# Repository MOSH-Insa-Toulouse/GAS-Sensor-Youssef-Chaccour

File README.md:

# MICRO-CONTROLLERS AND OPEN-SOURCE HARDWARE - Gas Sensor and LoRa Communication - Arduino Shield
This project was realized as part of "Microcontrollers and Open-Source Hardware" by Youssef Chaccour

# Goal
The goal of this project is to design a complete printed circuit board (PCB).
The circuit is then used with an Arduino board and a LoRa.
The collected data will be sent via the LoRa protocol on the TTN platform (The Things Network).

# Equipment
- Shield Gas Sensor
- Arduino uno
- LoRa module RN2483 breakout

# Features
- Gas sensor with connection (Requiring completion AIME)
- Adaptation circuit of the gas sensor to the ADC of the Arduino UNO:
- Filtering noises containing 2 passive filters and an active filter with AOP LTC1050
- Anti-aliasing filtering to perform ADC sampling
- Adaptation of the caliber
 
# Contents
This project contains source code and design files:
- The schematic part, describing the implemented electronic circuit (components, routing of pins)
- The layout part, describing the shape of the map, the location of the various elements on it and the trajectory of the routing tracks.
- Arduino code for LoRa

# Schemas PCB
Schematic design:
Here are some features of the schema:
- The input resistor (R1) is a protection resistor, it protects the operational amplifier from electrostatic discharges. Moreover, it is associated with the capacitor C1 to filter the voltage noise.
- The circuit between the capacitor C1 and the resistor R2 allows us to filter the current noise.
- Resistor R3 is used to adapt our assembly to the correct size. The resistance R3 can be modified to better calibrate the assembly.
- I had set up an active filter thanks to the circuit between the capacitor C2 and the resistor R4 at the output of the amplifier.
The resistor R5 and the capacitor C4 constitute a low-pass filter at the output of the assembly.
Finally, the capacitor C3 filters the noise coming from the voltage input 5V.

# PCB footprint on KiCad
Layout Design:
In order to realize the footprint correctly, I had to put into practice the following points:
- I chose a track width of 0.8 mm, so that the builder can achieve it with his equipment.
- I decided to insert only the RN2483 Breakout plate connector to optimize footprint space. Especially since we consider that the RN2483 card will not be directly integrated on the shield but connected by wires (connector).
- I used a layer of GND on the back of the plate allowing us to further optimize our space by reducing the number of connections.

Also, I have attached solution of the “exercise 5” (In Real Folder and requested by Mr. Jeremie Grisolia), as this exercise summarize the hole course, choosing the best technology with the least error.

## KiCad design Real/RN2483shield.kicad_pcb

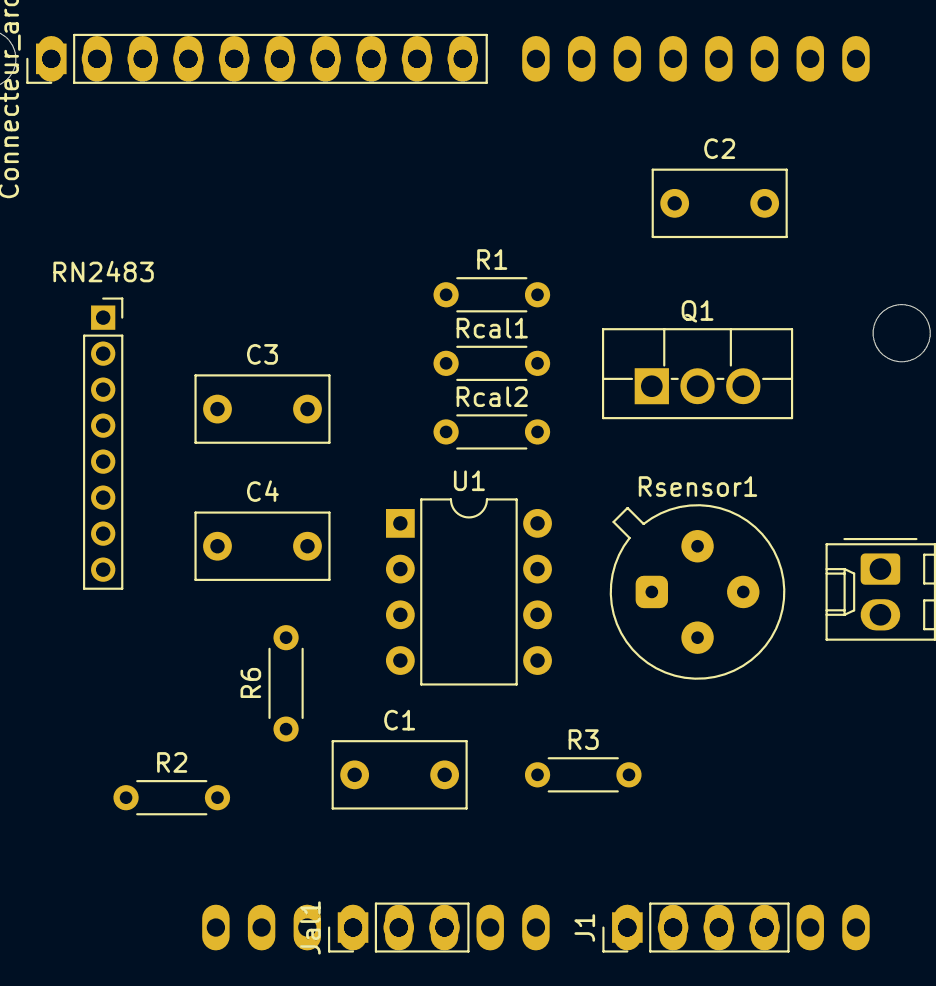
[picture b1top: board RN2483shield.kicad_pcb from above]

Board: 2 copper layers, 19 parts (0 on the bottom side), 14 nets, no tracks yet.

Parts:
C1, C2, C3: 100n; C_Rect_L7.2mm_W3.5mm_P5.00mm_FKS2_FKP2_MKS2_MKP2
C4: 1u; C_Rect_L7.2mm_W3.5mm_P5.00mm_FKS2_FKP2_MKS2_MKP2
Connecteur_arduino1: Conn_01x10; PinHeader_1x10_P2.54mm_Vertical
J1: Conn_01x04_Male; PinHeader_1x04_P2.54mm_Vertical
J2: Alim Vin; Molex_KK-254_AE-6410-02A_1x02_P2.54mm_Vertical
Jal1: alim conn; PinHeader_1x03_P2.54mm_Vertical
Q1: 2N2219; TO-220F-3_Vertical
R1: 10k; R_Axial_DIN0204_L3.6mm_D1.6mm_P5.08mm_Horizontal
R2, R3: 100k; R_Axial_DIN0204_L3.6mm_D1.6mm_P5.08mm_Horizontal
R6: 1k; R_Axial_DIN0204_L3.6mm_D1.6mm_P5.08mm_Horizontal
RN2483: Conn femelle RN2483; PinSocket_1x08_P2.00mm_Vertical
Rcal1, Rcal2: R; R_Axial_DIN0204_L3.6mm_D1.6mm_P5.08mm_Horizontal
Rsensor1: Fan_CPU_4pin; TO-5-4pro
SHIELD1: ARDUINO_SHIELD; ARDUINO_SHIELD_NOICSP
U1: LTC1050ACN8#PBF; DIP-8_W7.62mm

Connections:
+3V3: Jal1.1, RN2483.6, Rsensor1.2
+5V: C3.1, Jal1.2, U1.7
GAS: C2.1, J1.3, R6.1
GND: C1.2, C2.2, C3.2, J2.2, Jal1.3, R2.2, RN2483.8, Rcal2.2, Rsensor1.3, SHIELD1.GND2, SHIELD1.GND3, U1.4
unnamed: C1.1, R1.2, R2.1, U1.3
unnamed: C4.1, R3.1, R6.2, U1.6
unnamed: C4.2, R3.2, Rcal1.1, U1.2
unnamed: Connecteur_arduino1.10, Q1.2
unnamed: J2.1, Q1.3
unnamed: Q1.1, Rsensor1.4
unnamed: R1.1, Rsensor1.1
unnamed: Rcal1.2, Rcal2.1
RX: Connecteur_arduino1.8, RN2483.2
TX: Connecteur_arduino1.7, RN2483.1
